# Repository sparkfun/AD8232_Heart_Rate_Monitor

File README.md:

SparkFun AD8232 Single Lead Heart Rate Monitor
-------------------

[*AD8232 Single Lead Heart Rate Monitor (SEN-12650)*](https://www.sparkfun.com/products/12650)

The AD8232 is a neat little chip used to measure the electrical activity of the heart. This electrical activity can be charted as an ECG or Electrocardiogram. [Electrocardiography](http://en.wikipedia.org/wiki/Electrocardiography) is used to help diagnose various heart conditions. [The datasheet can be found here.](https://cdn.sparkfun.com/datasheets/Sensors/Biometric/AD8232.pdf)

This part was created in Eagle v6.5.0. 

Repository Contents
-------------------

* **/Fritzing** - Fritzing Example wiring images
* **/Hardware** - All Eagle design files (.brd, .sch)
* **/Production** - production panel files
* **/SPICE** - LTspice schematic
* **/Software** - Demo program files for hookup guide

Documentation
--------------
* **[Hookup Guide](https://learn.sparkfun.com/tutorials/ad8232-heart-rate-monitor-hookup-guide/)** - Basic hookup guide AD8232 heart rate monitor.

Version History
---------------
* [v10](https://github.com/sparkfun/AD8232_Heart_Rate_Monitor/tree/v10) Initial Release

License Information
-------------------
The hardware is released under [Creative Commons Share-alike 3.0](http://creativecommons.org/licenses/by-sa/3.0/).  
All other code is open source so please feel free to do anything you want with it; you buy me a beer if you use this and we meet someday ([Beerware license](http://en.wikipedia.org/wiki/Beerware)).

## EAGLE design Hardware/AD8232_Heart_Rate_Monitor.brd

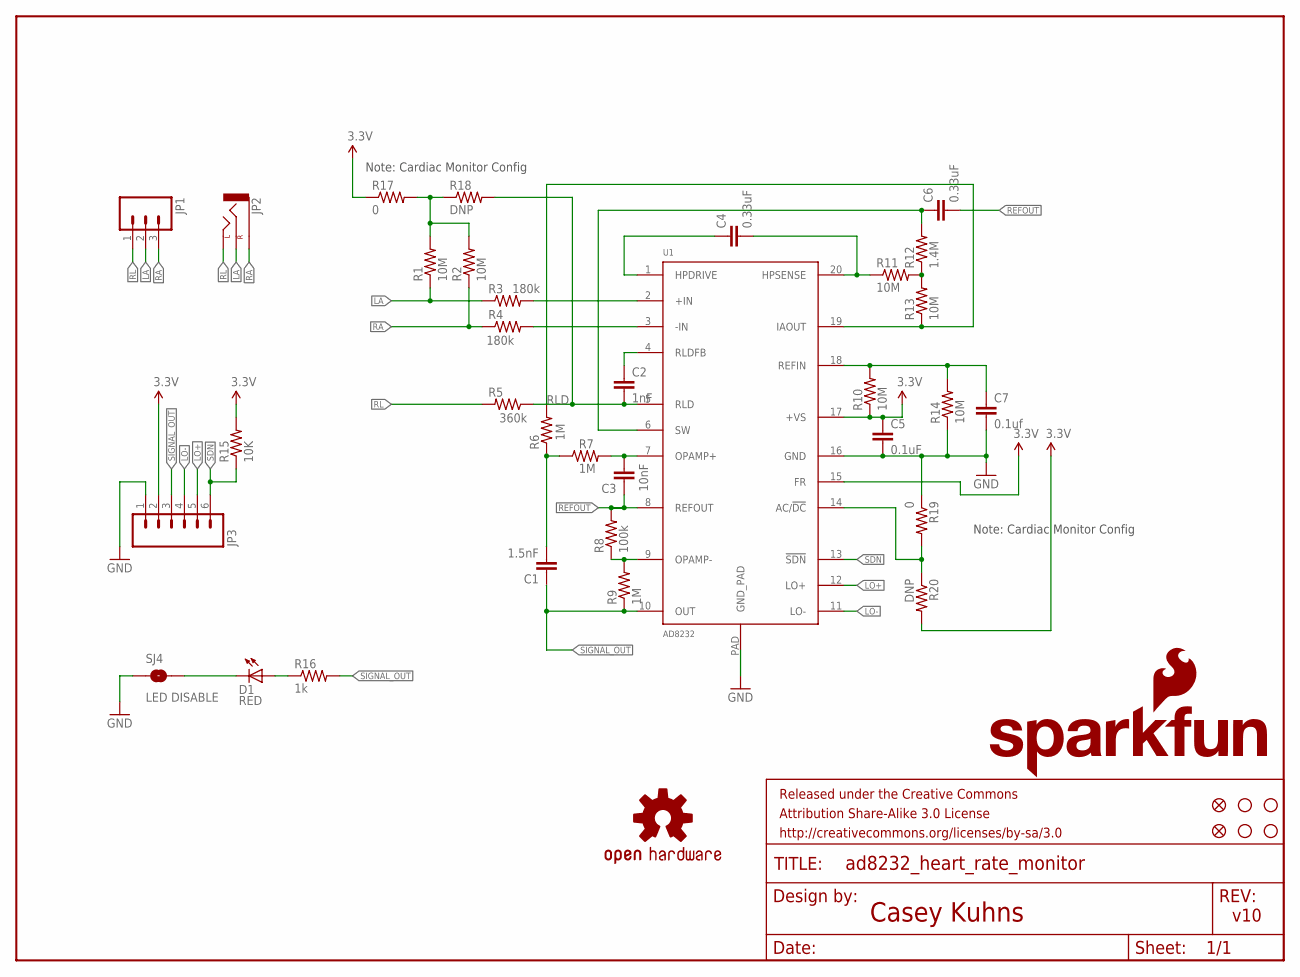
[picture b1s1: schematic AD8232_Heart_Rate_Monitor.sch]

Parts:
C1: 1.5nF; 0603-CAP
C2: 1nF; 0603-CAP
C3: 10nF; 0603-CAP
C4, C6: 0.33uF; 0805
C5: 0.1uF; 0603-CAP
C7: 0.1uf; 0603-CAP
D1: RED; LED-0603
FID1, FID2: FIDUCIAL1X2; FIDUCIAL-1X2
FRAME1: FRAME-LETTER; CREATIVE_COMMONS
JP1: M03PTH; 1X03
JP2: AUDIO-JACKSMD2; AUDIO-JACK-3.5MM-SMD
JP3: M06SIP; 1X06
LOGO1: OSHW-LOGOS; OSHW-LOGO-S
LOGO2: SFE_LOGO_NAME_FLAME.1_INCH; SFE_LOGO_NAME_FLAME_.1
R1, R2, R10, R11, R13, R14: 10M; 0603-RES
R3, R4: 180k; 0603-RES
R5: 360k; 0603-RES
R6, R7, R9: 1M; 0603-RES
R8: 100k; 0603-RES
R12: 1.4M; 0603-RES
R15: 10K; 0603-RES
R16: 1k; 0603-RES
R17, R19: 0; 0603
R18, R20: DNP; 0603
SJ4: LED DISABLE; SJ_2S-TRACE
STANDOFF1, STANDOFF2, STANDOFF3, STANDOFF4: STAND-OFF
U1: AD8232; LFCSP_20

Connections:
3.3V: C5.1, JP3.2, R10.1, R15.2, R17.1, R20.2, U1.15 (FR), U1.17 (+VS)
GND: C5.2, C7.2, JP3.1, R14.1, R19.1, SJ4.1, U1.16 (GND), U1.PAD (GND_PAD)
LA: JP1.2, JP2.RING (RIGHT), R1.1, R3.1
LO+: JP3.5, U1.12 (LO+)
LO-: JP3.4, U1.11 (LO-)
unnamed: R3.2, U1.2 (+IN)
unnamed: R4.2, U1.3 (-IN)
unnamed: C3.2, R7.2, U1.7 (OPAMP+)
unnamed: C4.2, R11.1, U1.20 (HPSENSE)
unnamed: C7.1, R10.2, R14.2, U1.18 (REFIN)
unnamed: D1.A, R16.1
unnamed: R8.1, R9.2, U1.9 (OPAMP-)
unnamed: R6.2, R13.1, U1.19 (IAOUT)
unnamed: C1.2, R6.1, R7.1
unnamed: D1.C, SJ4.2
unnamed: R19.2, R20.1, U1.14 (AC/!DC)
unnamed: C4.1, U1.1 (HPDRIVE)
unnamed: R11.2, R12.1, R13.2
unnamed: C6.1, R12.2, U1.6 (SW)
unnamed: C2.1, U1.4 (RLDFB)
unnamed: R1.2, R2.2, R17.2, R18.1
RA: JP1.3, JP2.SLEEVE, R2.1, R4.1
REFOUT: C3.1, C6.2, R8.2, U1.8 (REFOUT)
RL: JP1.1, JP2.TIP (LEFT), R5.2
RLD: C2.2, R5.1, R18.2, U1.5 (RLD)
SDN: JP3.6, R15.1, U1.13 (!SDN)
SIGNAL_OUT: C1.1, JP3.3, R9.1, R16.2, U1.10 (OUT)

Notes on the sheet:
Casey Kuhns
v10
Note: Cardiac Monitor Config

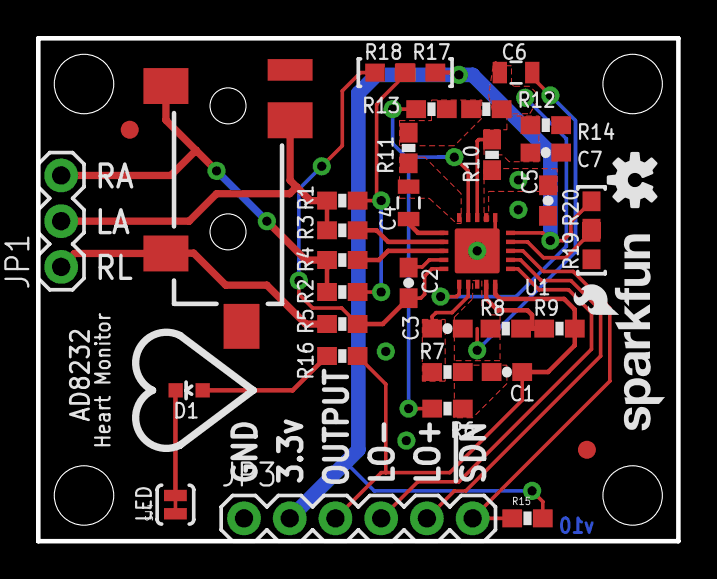
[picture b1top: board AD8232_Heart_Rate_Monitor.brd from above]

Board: 2 copper layers, 35.6 x 27.9 mm, 42 parts (0 on the bottom side), 27 nets.

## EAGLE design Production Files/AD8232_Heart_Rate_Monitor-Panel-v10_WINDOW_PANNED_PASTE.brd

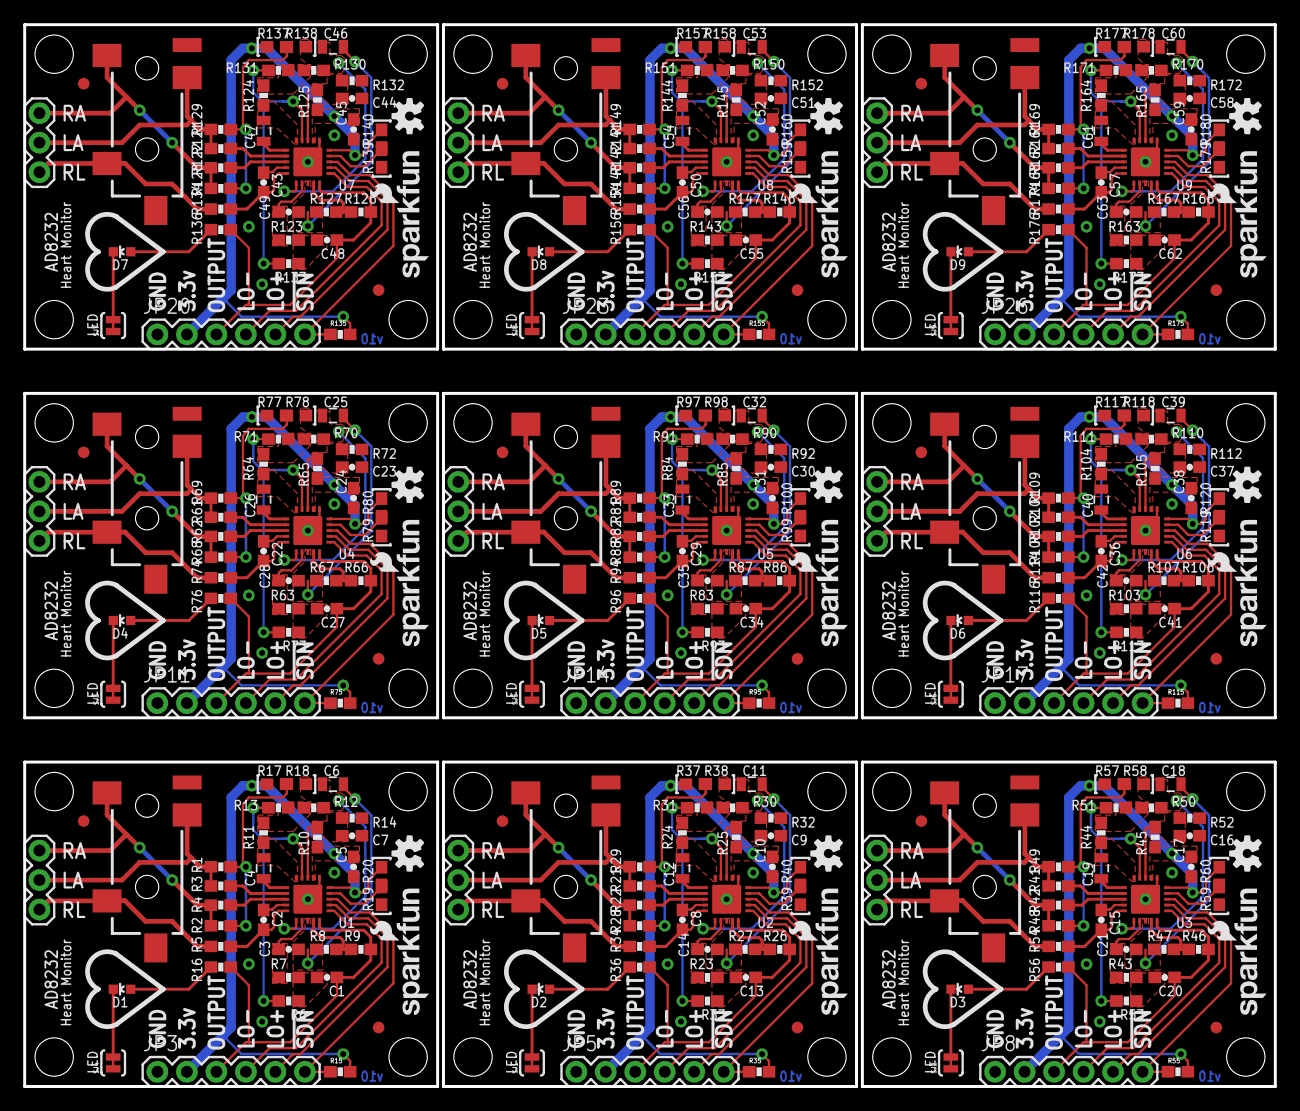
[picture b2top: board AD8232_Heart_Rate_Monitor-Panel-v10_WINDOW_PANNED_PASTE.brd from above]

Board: 2 copper layers, 107.7 x 91.4 mm, 369 parts (0 on the bottom side), 243 nets.

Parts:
C1, C13, C20, C27, C34, C41, C48, C55, C62: 1.5nF; 0603-CAP
C2, C8, C15, C22, C29, C36, C43, C50, C57: 1nF; 0603-CAP
C3, C14, C21, C28, C35, C42, C49, C56, C63: 10nF; 0603-CAP
C4, C6, C11, C12, C18, C19, C25, C26, C32, C33, C39, C40, C46, C47, C53, C54, C60, C61: 0.33uF; 0805
C5, C10, C17, C24, C31, C38, C45, C52, C59: 0.1uF; 0603-CAP
C7, C9, C16, C23, C30, C37, C44, C51, C58: 0.1uf; 0603-CAP
D1, D2, D3, D4, D5, D6, D7, D8, D9: RED; LED-0603
FID1, FID2, FID3, FID4, FID5, FID6, FID7, FID8, FID9, FID10, FID11, FID12, FID13, FID14, FID15, FID16, FID17, FID18: FIDUCIAL1X2; FIDUCIAL-1X2
JP1, JP6, JP9, JP12, JP15, JP18, JP21, JP24, JP27: 1X03
JP2, JP4, JP7, JP10, JP13, JP16, JP19, JP22, JP25: AUDIO-JACK-3.5MM-SMD
JP3, JP5, JP8, JP11, JP14, JP17, JP20, JP23, JP26: 1X06
LOGO1, LOGO4, LOGO6, LOGO8, LOGO10, LOGO12, LOGO14, LOGO16, LOGO18: OSHW-LOGOS; OSHW-LOGO-S
LOGO2, LOGO3, LOGO5, LOGO7, LOGO9, LOGO11, LOGO13, LOGO15, LOGO17: SFE_LOGO_NAME_FLAME.1_INCH; SFE_LOGO_NAME_FLAME_.1
R1, R2, R10, R11, R13, R14, R24, R25, R28, R29, R31, R32, R44, R45, R48, R49, R51, R52, R64, R65, R68, R69, R71, R72, R84, R85, R88, R89, R91, R92, R104, R105, R108, R109, R111, R112, R124, R125, R128, R129, R131, R132, R144, R145, R148, R149, R151, R152, R164, R165, R168, R169, R171, R172: 10M; 0603-RES
R3, R4, R21, R22, R41, R42, R61, R62, R81, R82, R101, R102, R121, R122, R141, R142, R161, R162: 180k; 0603-RES
R5, R34, R54, R74, R94, R114, R134, R154, R174: 360k; 0603-RES
R6, R7, R9, R23, R26, R33, R43, R46, R53, R63, R66, R73, R83, R86, R93, R103, R106, R113, R123, R126, R133, R143, R146, R153, R163, R166, R173: 1M; 0603-RES
R8, R27, R47, R67, R87, R107, R127, R147, R167: 100k; 0603-RES
R12, R30, R50, R70, R90, R110, R130, R150, R170: 1.4M; 0603-RES
R15, R35, R55, R75, R95, R115, R135, R155, R175: 10K; 0603-RES
R16, R36, R56, R76, R96, R116, R136, R156, R176: 1k; 0603-RES
R17, R19, R37, R39, R57, R59, R77, R79, R97, R99, R117, R119, R137, R139, R157, R159, R177, R179: 0; 0603
R18, R20, R38, R40, R58, R60, R78, R80, R98, R100, R118, R120, R138, R140, R158, R160, R178, R180: DNP; 0603
SJ1, SJ2, SJ3, SJ4, SJ5, SJ6, SJ7, SJ8, SJ9: LED DISABLE; SJ_2S-TRACE
STANDOFF1, STANDOFF2, STANDOFF3, STANDOFF4, STANDOFF5, STANDOFF6, STANDOFF7, STANDOFF8, STANDOFF9, STANDOFF10, STANDOFF11, STANDOFF12, STANDOFF13, STANDOFF14, STANDOFF15, STANDOFF16, STANDOFF17, STANDOFF18, STANDOFF19, STANDOFF20, STANDOFF21, STANDOFF22, STANDOFF23, STANDOFF24, STANDOFF25, STANDOFF26, STANDOFF27, STANDOFF28, STANDOFF29, STANDOFF30, STANDOFF31, STANDOFF32, STANDOFF33, STANDOFF34, STANDOFF35, STANDOFF36: STAND-OFF
U1, U2, U3, U4, U5, U6, U7, U8, U9: AD8232; LFCSP_20

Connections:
3.3V: C5.1, JP3.2, R10.1, R15.2, R17.1, R20.2, U1.15, U1.17
3.3V1: C10.1, JP5.2, R25.1, R35.2, R37.1, R40.2, U2.15, U2.17
3.3V2: C17.1, JP8.2, R45.1, R55.2, R57.1, R60.2, U3.15, U3.17
3.3V3: C24.1, JP11.2, R65.1, R75.2, R77.1, R80.2, U4.15, U4.17
3.3V4: C31.1, JP14.2, R85.1, R95.2, R97.1, R100.2, U5.15, U5.17
3.3V5: C38.1, JP17.2, R105.1, R115.2, R117.1, R120.2, U6.15, U6.17
3.3V6: C45.1, JP20.2, R125.1, R135.2, R137.1, R140.2, U7.15, U7.17
3.3V7: C52.1, JP23.2, R145.1, R155.2, R157.1, R160.2, U8.15, U8.17
3.3V8: C59.1, JP26.2, R165.1, R175.2, R177.1, R180.2, U9.15, U9.17
GND: C5.2, C7.2, JP3.1, R14.1, R19.1, SJ4.1, U1.16, U1.PAD
GND1: C9.2, C10.2, JP5.1, R32.1, R39.1, SJ1.1, U2.16, U2.PAD
GND2: C16.2, C17.2, JP8.1, R52.1, R59.1, SJ2.1, U3.16, U3.PAD
GND3: C23.2, C24.2, JP11.1, R72.1, R79.1, SJ3.1, U4.16, U4.PAD
GND4: C30.2, C31.2, JP14.1, R92.1, R99.1, SJ5.1, U5.16, U5.PAD
GND5: C37.2, C38.2, JP17.1, R112.1, R119.1, SJ6.1, U6.16, U6.PAD
GND6: C44.2, C45.2, JP20.1, R132.1, R139.1, SJ7.1, U7.16, U7.PAD
GND7: C51.2, C52.2, JP23.1, R152.1, R159.1, SJ8.1, U8.16, U8.PAD
GND8: C58.2, C59.2, JP26.1, R172.1, R179.1, SJ9.1, U9.16, U9.PAD
LA: JP1.2, JP2.RING, R1.1, R3.1
LA1: JP4.RING, JP6.2, R21.1, R29.1
LA2: JP7.RING, JP9.2, R41.1, R49.1
LA3: JP10.RING, JP12.2, R61.1, R69.1
LA4: JP13.RING, JP15.2, R81.1, R89.1
LA5: JP16.RING, JP18.2, R101.1, R109.1
LA6: JP19.RING, JP21.2, R121.1, R129.1
LA7: JP22.RING, JP24.2, R141.1, R149.1
LA8: JP25.RING, JP27.2, R161.1, R169.1
LO+: JP3.5, U1.12
LO+1: JP5.5, U2.12
LO+2: JP8.5, U3.12
LO+3: JP11.5, U4.12
LO+4: JP14.5, U5.12
LO+5: JP17.5, U6.12
LO+6: JP20.5, U7.12
LO+7: JP23.5, U8.12
LO+8: JP26.5, U9.12
LO-: JP3.4, U1.11
LO-1: JP5.4, U2.11
LO-2: JP8.4, U3.11
LO-3: JP11.4, U4.11
LO-4: JP14.4, U5.11
LO-5: JP17.4, U6.11
LO-6: JP20.4, U7.11
LO-7: JP23.4, U8.11
LO-8: JP26.4, U9.11
unnamed: R3.2, U1.2
unnamed: R4.2, U1.3
unnamed: C3.2, R7.2, U1.7
unnamed: C4.2, R11.1, U1.20
unnamed: C7.1, R10.2, R14.2, U1.18
unnamed: D1.A, R16.1
unnamed: R8.1, R9.2, U1.9
unnamed: R6.2, R13.1, U1.19
unnamed: C1.2, R6.1, R7.1
unnamed: D1.C, SJ4.2
unnamed: R19.2, R20.1, U1.14
unnamed: R21.2, U2.2
unnamed: C4.1, U1.1
unnamed: R11.2, R12.1, R13.2
unnamed: R22.2, U2.3
unnamed: C6.1, R12.2, R18.2, U1.6
unnamed: C2.1, U1.4
unnamed: C2.2, R5.1, U1.5
unnamed: C14.2, R23.2, U2.7
unnamed: R1.2, R2.2, R17.2, R18.1
unnamed: C12.2, R24.1, U2.20
unnamed: C9.1, R25.2, R32.2, U2.18
unnamed: R26.2, R27.1, U2.9
unnamed: C12.1, U2.1
unnamed: R24.2, R30.1, R31.2
unnamed: C11.1, R30.2, R38.2, U2.6
unnamed: C8.1, U2.4
unnamed: C13.2, R23.1, R33.1
unnamed: C8.2, R34.1, U2.5
unnamed: R31.1, R33.2, U2.19
unnamed: R28.2, R29.2, R37.2, R38.1
unnamed: D2.A, R36.1
unnamed: D2.C, SJ1.2
unnamed: R39.2, R40.1, U2.14
unnamed: R41.2, U3.2
unnamed: R42.2, U3.3
unnamed: C21.2, R43.2, U3.7
unnamed: C19.2, R44.1, U3.20
unnamed: C16.1, R45.2, R52.2, U3.18
unnamed: R46.2, R47.1, U3.9
unnamed: C19.1, U3.1
unnamed: R44.2, R50.1, R51.2
unnamed: C18.1, R50.2, R58.2, U3.6
unnamed: C15.1, U3.4
unnamed: C20.2, R43.1, R53.1
unnamed: C15.2, R54.1, U3.5
unnamed: R51.1, R53.2, U3.19
unnamed: R48.2, R49.2, R57.2, R58.1
unnamed: D3.A, R56.1
unnamed: D3.C, SJ2.2
unnamed: R59.2, R60.1, U3.14
unnamed: R61.2, U4.2
unnamed: R62.2, U4.3
unnamed: C28.2, R63.2, U4.7
unnamed: C26.2, R64.1, U4.20
unnamed: C23.1, R65.2, R72.2, U4.18
unnamed: R66.2, R67.1, U4.9
unnamed: C26.1, U4.1
unnamed: R64.2, R70.1, R71.2
unnamed: C25.1, R70.2, R78.2, U4.6
unnamed: C22.1, U4.4
unnamed: C27.2, R63.1, R73.1
unnamed: C22.2, R74.1, U4.5
unnamed: R71.1, R73.2, U4.19
unnamed: R68.2, R69.2, R77.2, R78.1
unnamed: D4.A, R76.1
unnamed: D4.C, SJ3.2
unnamed: R79.2, R80.1, U4.14
unnamed: R81.2, U5.2
unnamed: R82.2, U5.3
unnamed: C35.2, R83.2, U5.7
unnamed: C33.2, R84.1, U5.20
unnamed: C30.1, R85.2, R92.2, U5.18
unnamed: R86.2, R87.1, U5.9
unnamed: C33.1, U5.1
unnamed: R84.2, R90.1, R91.2
unnamed: C32.1, R90.2, R98.2, U5.6
unnamed: C29.1, U5.4
unnamed: C34.2, R83.1, R93.1
unnamed: C29.2, R94.1, U5.5
unnamed: R91.1, R93.2, U5.19
unnamed: R88.2, R89.2, R97.2, R98.1
unnamed: D5.A, R96.1
unnamed: D5.C, SJ5.2
unnamed: R99.2, R100.1, U5.14
unnamed: R101.2, U6.2
unnamed: R102.2, U6.3
unnamed: C42.2, R103.2, U6.7
unnamed: C40.2, R104.1, U6.20
unnamed: C37.1, R105.2, R112.2, U6.18
unnamed: R106.2, R107.1, U6.9
unnamed: C40.1, U6.1
unnamed: R104.2, R110.1, R111.2
unnamed: C39.1, R110.2, R118.2, U6.6
unnamed: C36.1, U6.4
unnamed: C41.2, R103.1, R113.1
unnamed: C36.2, R114.1, U6.5
unnamed: R111.1, R113.2, U6.19
unnamed: R108.2, R109.2, R117.2, R118.1
unnamed: D6.A, R116.1
unnamed: D6.C, SJ6.2
unnamed: R119.2, R120.1, U6.14
unnamed: R121.2, U7.2
unnamed: R122.2, U7.3
unnamed: C49.2, R123.2, U7.7
unnamed: C47.2, R124.1, U7.20
unnamed: C44.1, R125.2, R132.2, U7.18
unnamed: R126.2, R127.1, U7.9
unnamed: C47.1, U7.1
unnamed: R124.2, R130.1, R131.2
unnamed: C46.1, R130.2, R138.2, U7.6
unnamed: C43.1, U7.4
unnamed: C48.2, R123.1, R133.1
unnamed: C43.2, R134.1, U7.5
unnamed: R131.1, R133.2, U7.19
unnamed: R128.2, R129.2, R137.2, R138.1
unnamed: D7.A, R136.1
unnamed: D7.C, SJ7.2
unnamed: R139.2, R140.1, U7.14
unnamed: R141.2, U8.2
unnamed: R142.2, U8.3
unnamed: C56.2, R143.2, U8.7
unnamed: C54.2, R144.1, U8.20
unnamed: C51.1, R145.2, R152.2, U8.18
unnamed: R146.2, R147.1, U8.9
unnamed: C54.1, U8.1
unnamed: R144.2, R150.1, R151.2
unnamed: C53.1, R150.2, R158.2, U8.6
unnamed: C50.1, U8.4
unnamed: C55.2, R143.1, R153.1
unnamed: C50.2, R154.1, U8.5
unnamed: R151.1, R153.2, U8.19
unnamed: R148.2, R149.2, R157.2, R158.1
unnamed: D8.A, R156.1
unnamed: D8.C, SJ8.2
unnamed: R159.2, R160.1, U8.14
unnamed: R161.2, U9.2
unnamed: R162.2, U9.3
unnamed: C63.2, R163.2, U9.7
unnamed: C61.2, R164.1, U9.20
unnamed: C58.1, R165.2, R172.2, U9.18
unnamed: R166.2, R167.1, U9.9
unnamed: C61.1, U9.1
unnamed: R164.2, R170.1, R171.2
unnamed: C60.1, R170.2, R178.2, U9.6
unnamed: C57.1, U9.4
unnamed: C62.2, R163.1, R173.1
unnamed: C57.2, R174.1, U9.5
unnamed: R171.1, R173.2, U9.19
unnamed: R168.2, R169.2, R177.2, R178.1
unnamed: D9.A, R176.1
unnamed: D9.C, SJ9.2
unnamed: R179.2, R180.1, U9.14
RA: JP1.3, JP2.SLEEVE, R2.1, R4.1
RA1: JP4.SLEEVE, JP6.3, R22.1, R28.1
RA2: JP7.SLEEVE, JP9.3, R42.1, R48.1
RA3: JP10.SLEEVE, JP12.3, R62.1, R68.1
RA4: JP13.SLEEVE, JP15.3, R82.1, R88.1
RA5: JP16.SLEEVE, JP18.3, R102.1, R108.1
RA6: JP19.SLEEVE, JP21.3, R122.1, R128.1
RA7: JP22.SLEEVE, JP24.3, R142.1, R148.1
RA8: JP25.SLEEVE, JP27.3, R162.1, R168.1
REFOUT: C3.1, C6.2, R8.2, U1.8
REFOUT1: C11.2, C14.1, R27.2, U2.8
REFOUT2: C18.2, C21.1, R47.2, U3.8
REFOUT3: C25.2, C28.1, R67.2, U4.8
REFOUT4: C32.2, C35.1, R87.2, U5.8
REFOUT5: C39.2, C42.1, R107.2, U6.8
REFOUT6: C46.2, C49.1, R127.2, U7.8
REFOUT7: C53.2, C56.1, R147.2, U8.8
REFOUT8: C60.2, C63.1, R167.2, U9.8
RL: JP1.1, JP2.TIP, R5.2
RL1: JP4.TIP, JP6.1, R34.2
RL2: JP7.TIP, JP9.1, R54.2
RL3: JP10.TIP, JP12.1, R74.2
RL4: JP13.TIP, JP15.1, R94.2
RL5: JP16.TIP, JP18.1, R114.2
RL6: JP19.TIP, JP21.1, R134.2
RL7: JP22.TIP, JP24.1, R154.2
RL8: JP25.TIP, JP27.1, R174.2
SDN: JP3.6, R15.1, U1.13
SDN1: JP5.6, R35.1, U2.13
SDN2: JP8.6, R55.1, U3.13
SDN3: JP11.6, R75.1, U4.13
SDN4: JP14.6, R95.1, U5.13
SDN5: JP17.6, R115.1, U6.13
SDN6: JP20.6, R135.1, U7.13
SDN7: JP23.6, R155.1, U8.13
SDN8: JP26.6, R175.1, U9.13
SIGNAL_OUT: C1.1, JP3.3, R9.1, R16.2, U1.10
SIGNAL_OUT1: C13.1, JP5.3, R26.1, R36.2, U2.10
SIGNAL_OUT2: C20.1, JP8.3, R46.1, R56.2, U3.10
SIGNAL_OUT3: C27.1, JP11.3, R66.1, R76.2, U4.10
SIGNAL_OUT4: C34.1, JP14.3, R86.1, R96.2, U5.10
SIGNAL_OUT5: C41.1, JP17.3, R106.1, R116.2, U6.10
SIGNAL_OUT6: C48.1, JP20.3, R126.1, R136.2, U7.10
SIGNAL_OUT7: C55.1, JP23.3, R146.1, R156.2, U8.10
SIGNAL_OUT8: C62.1, JP26.3, R166.1, R176.2, U9.10

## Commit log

2013-11-14 Update README.md
    updated
2013-11-15 Initial board design
2013-11-21 Fixed silk and updated capacitors to appropriate sizes.
2013-11-21 Fixed cap values
2013-11-21 added name
2013-11-21 updated schematic in attempt to fix ERC errors
2013-11-21 Fixed file error
2014-01-14 Changes made
    1. Added signal output pin
    2. Added pull-up resistor on shutdown pin to keep chip active by default.
    3. Moved some labels around to let everything fit
    4. fixed exposed vias.
2014-01-14 Corrected chip orientation marker on board
2014-01-21 added connectors for user leads, added led for some visual.
2014-01-21 Updated components to match BOM
2014-01-21 changed jumpers to populatable jumpers makes for easy production changes
2014-01-22 added matched traces
2014-03-25 Changed layout in attempt to remove noise. Changed resistor values to help remove DC offset.
2014-05-02 Added fiducials
2014-05-07 fixed Rev Numbers
2014-05-07 Readme updated
2014-05-08 fixed solder paste isssue with AD8232
2014-05-12 created panel v10
2014-06-27 added example code
2014-07-03 cleaned up processing and arduino sketches
2014-07-03 delected files
2014-07-09 fritzing parts worked on
2014-07-15 General File cleanup
2014-07-15 Updated URL in Readme
2014-07-15 Fixed typo
2015-01-15 Updated Readme.
2015-11-12 fixed broken link to datasheet
    links without `//` are relative, the datasheet link pointed to `https://github.com/sparkfun/AD8232_Heart_Rate_Monitor/blob/master/www.sparkfun.com`. Now it links to the datasheet itself.
2016-09-30 Adjusted paste on IC
    Note, I only adjusted the PRODUCTION panel file.
    Changed from single cirlce of paste under IC, to a window panned style.
    Reduced paste to 75% coverage on all outer pads on IC.
    Adjusted package lives in TEMP library in this repo.
    Also, kept original production BRD file for v10 for history.
    The new file "WINDOW_PANNED_PASTE" is intended to only be userd to buy a
2017-04-28 Create HRT_MNT_P3
    Here are proposed changes for the code of the heart rate monitor, the old code could only function in the second version of Processing. The proposed changes now work for the newest version (3.3.2). I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
    **Side-Note**
    The only hiccup I encountered in modifying the code and comparing it to the old one's readings was that when it is supposed to be flat-line there is a negative charge that is registered, which was no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
2018-05-30 Fix warnings
2018-05-31 R18 must be connected to RLD instead of SW
2018-07-11 Processing 3.3 Compatability Update
    Moved code that draws data from serialEvent to draw. Tested compatibility with Processing 2.2 and 3.3.7.
2018-07-16 Added BPM functionality
    Added functionality to calculate and display BPM.
2018-07-16 Documentation and formatting
    Added comments for clarity, changed formatting for better uniformity.
2019-04-29 Corrected Fritzing Diagram
2021-06-14 1) Reduced the size of array to compute the average BPM 2) Fix identations 3) Fix the bug when calculateBPM() gets diff equals to zero 4) Increase the window size for better view 5) Fix the "Ariel" f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
2021-09-12 NEW ECG
2025-05-12 Add LTspice schematics for AD8232_Heart_Rate_Monitor
2025-05-12 Add LTspice schematics

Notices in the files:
parts and their libraries:
SparkFun-Aesthetics: Licensing: CC v3.0 Share-Alike You are welcome to use this library for commercial purposes.
SparkFun-Aesthetics: Released under the Creative Commons Attribution Share-Alike 3.0 License
SparkFun-Aesthetics: Released under the Creative Commons
